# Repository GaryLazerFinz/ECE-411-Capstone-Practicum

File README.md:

# ECE-411-Capstone-Practicum
Group 8's Practicum Repository  

We have designed a inexpensive and simple fan using a micocontroller and a custom built pcb. 
  
Parts Required  
1 10k resistor smd  
1 1k resistor smd  
3 100n Capacitors smd or th  
1 5 volt Voltage Converter th  
1 ATtiny85 MCU th  
1 2n4001 Diode th  
9 volt Battery Connector  
1 5 V DC Motor  
Analog Temperature Sensor  
Arduino UNO for ISP programming

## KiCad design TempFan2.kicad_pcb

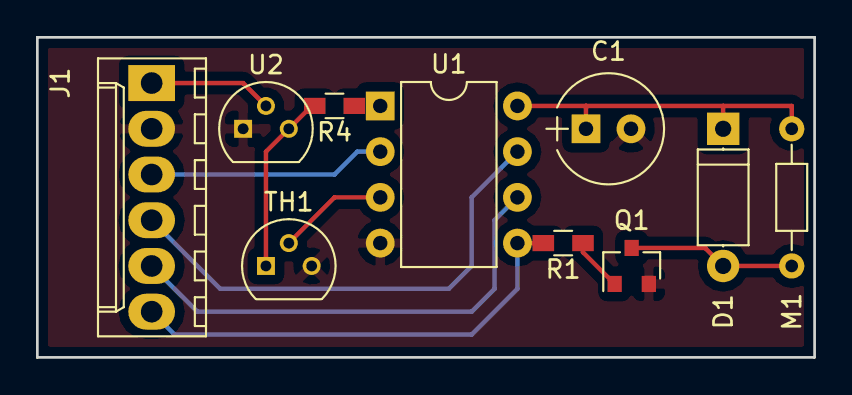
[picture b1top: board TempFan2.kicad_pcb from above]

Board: 2 copper layers, 43.2 x 17.8 mm, 10 parts (0 on the bottom side), 11 nets.

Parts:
C1: 100 u; CP_Radial_Tantal_D6.0mm_P2.50mm
D1: D; D_A-405_P7.62mm_Horizontal
J1: Conn_01x06; Molex_KK-6410-06_06x2.54mm_Straight
M1: Fan; R_Axial_DIN0204_L3.6mm_D1.6mm_P7.62mm_Horizontal
Q1: NPN; SOT-23
R1: 1 k; R_0603_HandSoldering
R4: 100; R_0603_HandSoldering
TH1: Temp Sensor; TO-92_Molded_Narrow
U1: ATTINY85; DIP-8_W7.62mm
U2: 5V Reg; TO-92_Molded_Narrow

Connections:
+5V: C1.1, D1.1, M1.1, R4.2, TH1.1, U1.8, U2.3
+9V: J1.1, U2.2
GND: C1.2, J1.2, Q1.2, TH1.3, U1.4, U2.1
unnamed: D1.2, M1.2, Q1.3
unnamed: Q1.1, R1.1
unnamed: R4.1, U1.1
unnamed: TH1.2, U1.3
Out1: J1.3, U1.2
Out2: J1.4, U1.7
Out3: J1.5, U1.6
Out4: J1.6, R1.2, U1.5

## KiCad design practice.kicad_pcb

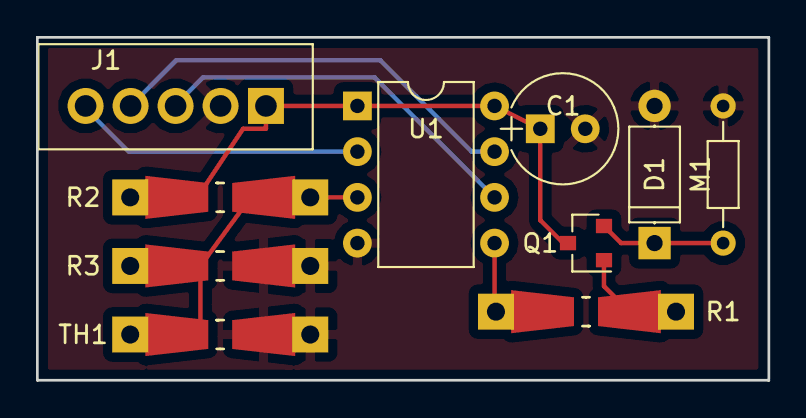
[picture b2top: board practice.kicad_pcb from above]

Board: 2 copper layers, 40.6 x 19.0 mm, 10 parts (0 on the bottom side), 9 nets.

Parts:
C1: 100 u; CP_Radial_Tantal_D6.0mm_P2.50mm
D1: D; D_A-405_P7.62mm_Horizontal
J1: Conn_01x05; Wafer_Vertical15x5.8x7RM2.5-5
M1: Fan; R_Axial_DIN0204_L3.6mm_D1.6mm_P7.62mm_Horizontal
Q1: NPN; SOT-23
R1: 1K; Resistor_SMD+THTuniversal_0805to1206_RM10_HandSoldering
R2, R3: 10K; Resistor_SMD+THTuniversal_0805to1206_RM10_HandSoldering
TH1: NTC; Resistor_SMD+THTuniversal_0805to1206_RM10_HandSoldering
U1: ATTINY85; DIP-8_W7.62mm

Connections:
+5V: C1.1, J1.1, Q1.3, R2.1, U1.1, U1.8
GND: C1.2, D1.2, J1.2, M1.2, R3.2, TH1.2, U1.4
unnamed: D1.1, M1.1, Q1.2
unnamed: Q1.1, R1.1
unnamed: R1.2, U1.5
unnamed: R2.2, R3.1, TH1.1, U1.3
Out1: J1.3, U1.6
Out2: J1.4, U1.7
Out3: J1.5, U1.2

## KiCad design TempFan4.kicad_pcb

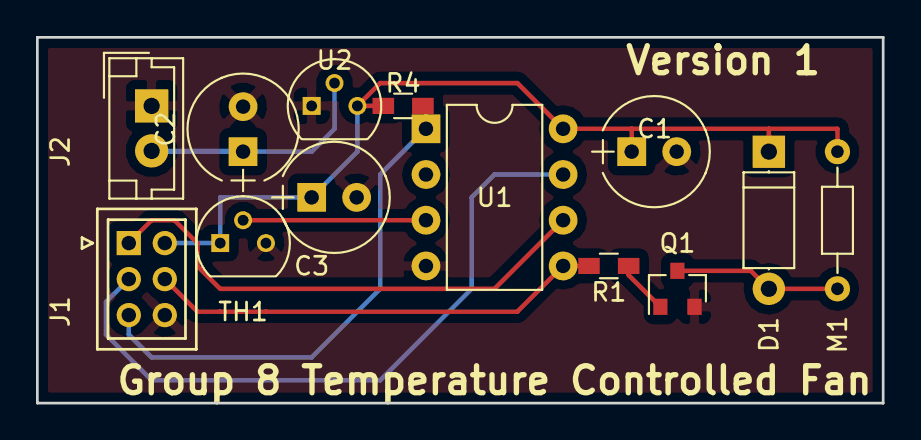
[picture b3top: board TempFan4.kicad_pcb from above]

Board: 2 copper layers, 47.0 x 20.3 mm, 13 parts (0 on the bottom side), 10 nets.

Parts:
C1: 100n; CP_Radial_Tantal_D6.0mm_P2.50mm
C2, C3: 10u; CP_Radial_Tantal_D6.0mm_P2.50mm
D1: D; D_A-405_P7.62mm_Horizontal
J1: Conn_01x06; JAE_LY20-06P-2T_2x03x2.00mm_Straight
J2: Conn_01x02; JST_EH_B02B-EH-A_02x2.50mm_Straight
M1: Fan; R_Axial_DIN0204_L3.6mm_D1.6mm_P7.62mm_Horizontal
Q1: NPN; SOT-23
R1: 1 k; R_0603_HandSoldering
R4: >10k; R_0603_HandSoldering
TH1: MCP9700A-E/TO; TO-92_Molded_Narrow
U1: ATTINY85; DIP-8_W7.62mm
U2: 5V Reg L7805CV; TO-92_Molded_Narrow

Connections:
+5V: C1.1, C3.1, D1.1, J1.4, M1.1, R4.2, TH1.1, U1.8, U2.3
+9V: C2.1, J2.2, U2.2
GND: C1.2, C2.2, C3.2, J1.6, J2.1, Q1.2, TH1.3, U1.4, U2.1
MISO: J1.1, U1.6
MOSI: J1.5, R1.2, U1.5
unnamed: D1.2, M1.2, Q1.3
unnamed: Q1.1, R1.1
unnamed: TH1.2, U1.3
RESET: J1.3, R4.1, U1.1
SCK: J1.2, U1.7

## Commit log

2017-10-06 Read an analogue voltage
    Read an analogue voltage on analogue channel 0 and flash a LED on output B.1 when higher than a value of 50
    From
    http://www.picaxe.com/BASIC-Commands/Analogue-InputOutput/readadc/
2017-10-06 Generate bursts of PWM
    Generate a burst of PWM on output pin 4 every 20ms
    From
    http://www.picaxe.com/BASIC-Commands/Digital-InputOutput/pwm/
2017-10-09 Tip 125 motor circuit
    https://www.google.com/search?q=tip+125+motor+cicuit&oq=tip+125+motor+cicuit&aqs=chrome..69i57j33.11254j0j7&client=tablet-android-samsung&sourceid=chrome-mobile&ie=UTF-8#imgrc=hfDhz4coRwulHM:
2017-10-09 PICAXE Programming Circuit
    https://www.gammon.com.au/forum/bbshowpost.php?bbsubject_id=10868
2017-10-09 Case statement
    I think the case value to value (line 6) will be useful
2017-10-09 Temp control for picaxe
    This should be pretty close to what we need to use.
2017-10-09 Add files via upload
    Pics of the prototype I made
2017-10-10 Programming Circuit for the PICAXE
2017-10-13 Some files about digital display
    em... I am not sure it will work as we want because it also need the push bottom input. The part we can consider is the clock code which turn on the digital display. The code is Verilog and the softw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
2017-10-18 AA battery life Duracell
2017-10-25 The ATtiny85 trinket datasheet
2017-10-25 The code from the Trinket datasheet
2017-10-25 The ATtiny 85 datasheet
2017-10-26 One idea for the temperature controlled fan.
2017-10-26 Alternate Eagle Temp Fan
2017-11-02 Project Schedule
2017-11-02 Schedule
2017-11-02 ProjSched microsoft proj file
2017-11-02 Project_schedule_screencap
2017-11-02 dates for schedule2
2017-11-03 Empty schedule
2017-11-03 Testing
2017-11-03 Wrong file
2017-11-03 PCB Layouts and pics
2017-11-08 Block diagrams
2017-11-08 temp_fan_eagle_schematic
2017-11-09 Prototype2
2017-11-09 Tables for block diagrams
2017-11-14 Original Kicad files
2017-11-15 Tempfan2.0
2017-11-15 Temp Fan control
2017-11-15 TempFan3.0
2017-11-16 Final Temp Fan Layout
2017-11-16 Final Designs
2017-11-16 Final Layout
2017-11-18 Prototype 3
2017-11-18 Initial code
    This code turns the fan on with a warm breath. I assume around 98°F
2017-11-23 ATMEL Temperature controlled fan example from the MICROCHIP site
    http://www.microchip.com//wwwAppNotes/AppNotes.aspx?appnote=en591474
2017-11-23 ATMEL temperatured controled fan example
2017-11-23 Pulse Width Modulation Example
    Taken from
    https://www.marcelpost.com/wiki/index.php/ATtiny85_PWM
2017-11-23 Reading a voltage level
    Taken from
    https://www.marcelpost.com/wiki/index.php/ATtiny85_ADC
2017-12-01 Test plan
2017-12-07 Final Blocks
2017-12-07 Final Wiki Pics
2017-12-07 wiki fixs
2017-12-07 KiCad Files
2017-12-07 Temperature Fan Software
2017-12-07 Temp Fan Software
